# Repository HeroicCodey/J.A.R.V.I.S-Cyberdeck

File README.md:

# J.A.R.V.I.S-Cyberdeck
An Esp32 Based Cyberdeck using 1.8 inch TFT and four buttons (And of course 30 pin ESP-32).

The "Atlantis V2" project is a Tier 3 custom-built, portable ESP32-based cyberdeck and smart device system, featuring a firmware environment dubbed "J.A.R.V.I.S. Core V.01" or "Retro-OS". Designed by pilot/operator Sloke Bhattacharyya, the project functions as a multi-module tactical terminal integrated with cellular and network diagnostics, arcade games, and productivity tools.

**Hardware Specifications**

* **Microcontroller:** The system is powered by an ESP32 Development Board, specifically a NodeMCU-32S or ESP32-WROOM-32.
* **Display:** It utilizes a 1.8-inch SPI TFT LCD Display driven by an ST7735 controller with a 128x160 pixel resolution.
* **Input Interface:** Navigation is handled by a physical matrix of four tactile push buttons mapped to Nav, Prev, Select, and Back actions.
* **Connectivity Hardware:** Cellular capabilities are provided by an A7670C 4G LTE Module using a UART2 interface.
* **Power Architecture:** The device runs on a single 18650 Lithium-ion battery cell paired with a TP4056/BMS protection board.

**User Interface and Display Design**

* **Aesthetic Paradigm:** The interface is modeled after a simplistic, monochromatic Linux terminal.
* **Menu System:** Navigation relies on a horizontal camera-roll carousel featuring an animated viewfinder box to highlight active selections.
* **Display Orientation:** The software enforces a 180-degree display rotation (`tft.setRotation(2)`) to accommodate the physical mounting orientation of the screen.
* **Theme Engine:** The UI supports custom color palettes, including "OBSIDIAN" (black with magenta highlights), "MATRIX" (black with emerald green), and "LAPIS" (obsidian base with cyan-dominant telemetry).

**Software Modules and Applications**

* **Boot Sequence:** The system features a multi-stage fake Linux boot sequence, complete with rootfs mounting, SPI initialization, a CRT beam raster expansion effect, and an encrypted "HELLO SLOKE" operator greeting.
* **E.D.I.T.H. Tactical Diagnostics:** A dedicated network module capable of WiFi access point scanning, subnet discovery (pinging local IPs to map active hosts), and RSSI signal mapping.
* **F.R.I.D.A.Y. Web Portal:** The ESP32 hosts a local Access Point and web server that allows users to remotely configure WiFi credentials, manage a tactical "To-Do" directive list, and upload text files (TXT, JSON, CSV) directly to the device's LittleFS flash storage.
* **Productivity Tools:** The firmware includes a built-in text reader for displaying uploaded files, a virtual on-screen keyboard for standalone text entry, and a clock application featuring NTP network time synchronization, a countdown timer, and a stopwatch.
* **Arcade Games Suite:** The device includes a fully persistent, high-score tracking game engine containing six titles:
* *Space Impact:* A vertical space shooter featuring progressive difficulty, drone and interceptor enemy classes, and a dynamic spawn rate.
* *Cyber Snake:* A classic grid-based snake game.
* *Cyber Bird:* A physics-based Flappy Bird clone.
* *Firewall Breach:* A Breakout-style block-busting game.
* *Neon Overdrive:* A three-lane vertical racing/dodging game.
* *Lunar Descent:* A physics-based lunar lander simulation requiring precise thrust and angle management.

[BOM.csv](https://github.com/user-attachments/files/33223327/BOM.csv)

[Atlantis V2.pdf](https://github.com/user-attachments/files/33223259/Atlantis.V2.pdf)
Item No.,Part Name,Quantity
1,ESP32 30-pin,1
2,4-pin Tactile Button,4
3,1.8 in Touchless TFT,1

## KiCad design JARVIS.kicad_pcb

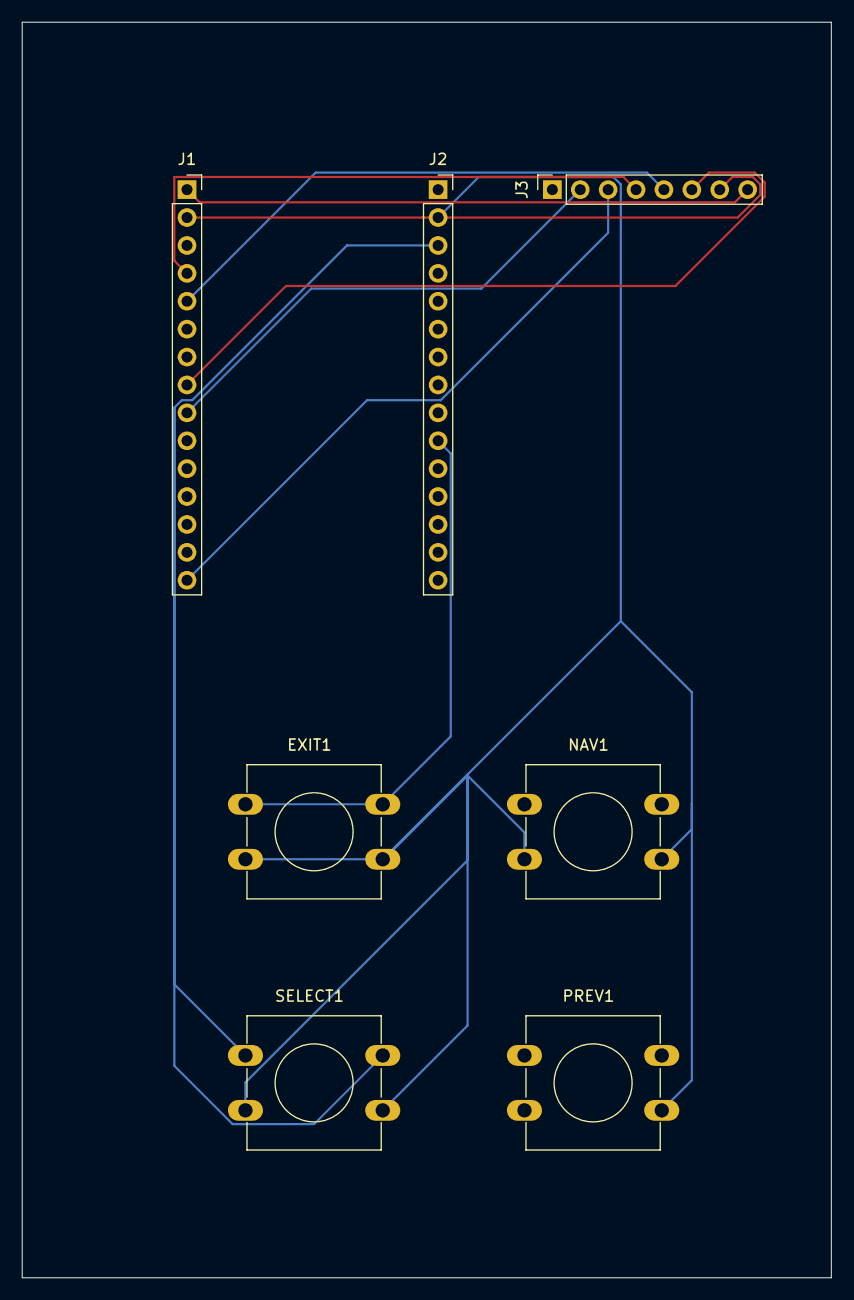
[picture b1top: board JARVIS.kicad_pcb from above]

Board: 4 copper layers, 73.7 x 114.3 mm, 7 parts (0 on the bottom side), 11 nets.

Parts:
EXIT1: SW_Push; SW_PUSH-12mm
J1, J2: Conn_01x15; PinSocket_1x15_P2.54mm_Vertical
J3: Conn_01x08; PinSocket_1x08_P2.54mm_Vertical
NAV1: SW_Push; SW_PUSH-12mm
PREV1: SW_Push; SW_PUSH-12mm
SELECT1: SW_Push; SW_PUSH-12mm

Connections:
/3v3: J1.1, J3.1, J3.8
/D2: J1.4, J3.4
/D4: J1.5, J3.5
/D5: J1.8, J3.6
/D13: J2.3, SELECT1.1
/D14: J2.5, NAV1.1
/D18: J1.9, J3.2
/D23: J1.15, J3.3
/D27: J2.6, PREV1.1
/D32: EXIT1.1, J2.10
GND: EXIT1.2, J1.2, J2.2, J3.7, NAV1.2, PREV1.2, SELECT1.2
